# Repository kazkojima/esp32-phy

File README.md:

# ESP32 PHY

## hardware

ESP-WROOM-32 board with Ethernet made with KiCAD

  * esp32-tlk110

  * esp32-wslan8720

  There are choices for esp32-wslan8720 board. See 

https://kazkojima.github.io/esp32-phy2.html

for detail.

## apps

Applications with ESP32 PHY.

  * sbusconv - A serial to ether converter

See README in the application directory for detail.

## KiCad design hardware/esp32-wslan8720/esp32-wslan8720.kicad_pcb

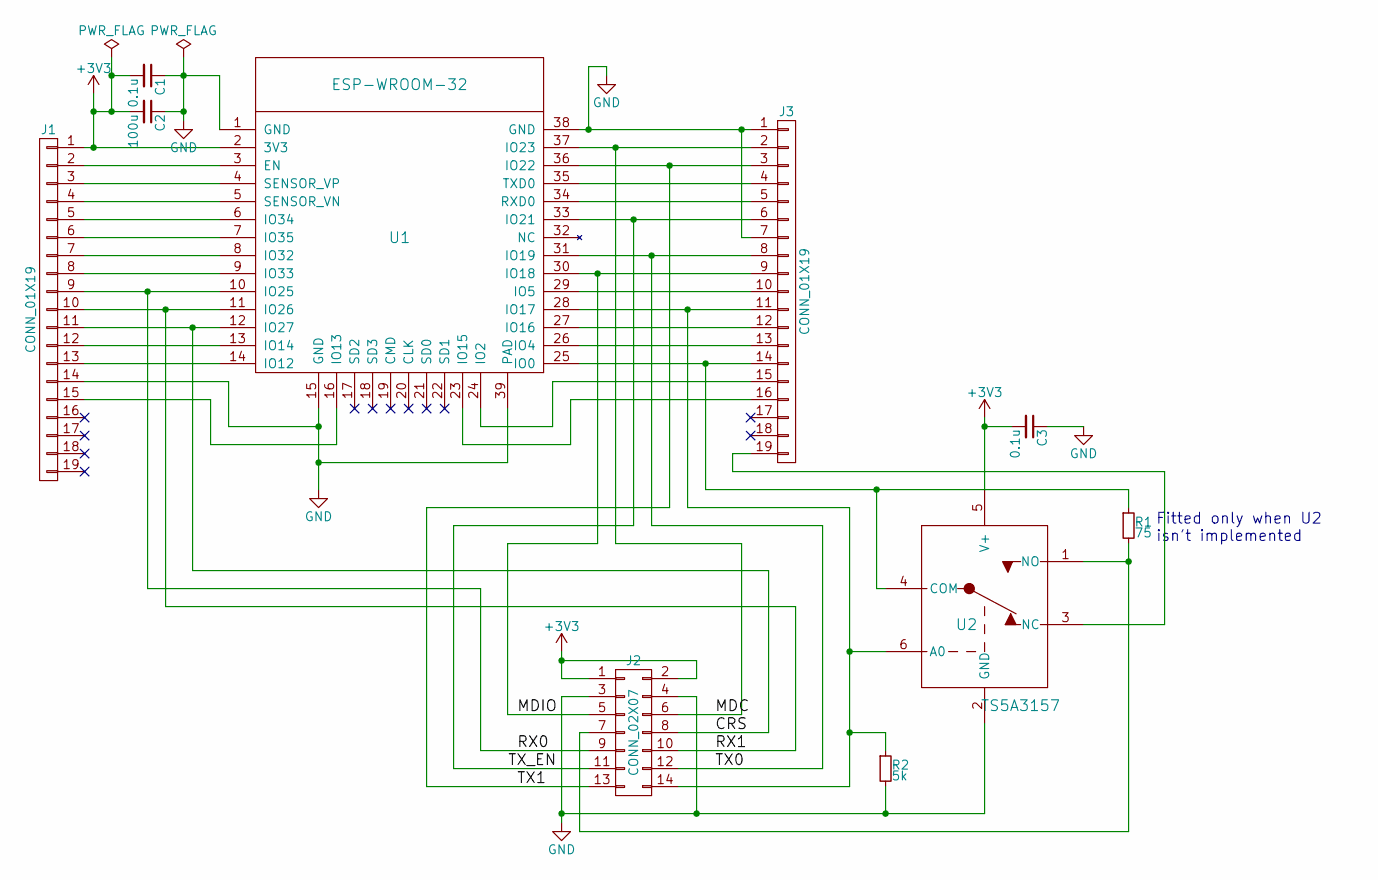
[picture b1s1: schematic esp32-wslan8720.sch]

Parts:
C1, C3: 0.1u; C_0603_HandSoldering
C2: 100u; C_1210_HandSoldering
J1, J3: CONN_01X19; Pin_Header_Straight_1x19_Pitch2.54mm
J2: CONN_02X07; Pin_Header_Angled_2x07_Pitch2.54mm
R1: 75; R_0603_HandSoldering
R2: 5k; R_0603_HandSoldering
U1: ESP-WROOM-32; ESP32-WROOM-fixed
U2: TS5A3157; SOT-23-6_Handsoldering

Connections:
+3V3: C1.2, C2.2, C3.2, J1.1, J2.1, J2.2, U1.2 (3V3), U2.5 (V+)
/CRS: J1.11, J2.8, U1.12 (IO27)
/MDC: J2.6, J3.2, U1.37 (IO23)
/MDIO: J2.5, J3.9, U1.30 (IO18)
/RX0: J1.9, J2.9, U1.10 (IO25)
/RX1: J1.10, J2.10, U1.11 (IO26)
/TX0: J2.12, J3.8, U1.31 (IO19)
/TX1: J2.13, J3.3, U1.36 (IO22)
/TX_EN: J2.11, J3.6, U1.33 (IO21)
GND: C1.1, C2.1, C3.1, J1.14, J2.3, J2.4, J3.1, J3.7, R2.2, U1.1 (GND), U1.15 (GND), U1.38 (GND), U1.39 (PAD), U2.2 (GND)
unnamed: J1.2, U1.3 (EN)
unnamed: J1.3, U1.4 (SENSOR_VP)
unnamed: J1.4, U1.5 (SENSOR_VN)
unnamed: J1.5, U1.6 (IO34)
unnamed: J1.6, U1.7 (IO35)
unnamed: J1.7, U1.8 (IO32)
unnamed: J1.8, U1.9 (IO33)
unnamed: J1.12, U1.13 (IO14)
unnamed: J1.13, U1.14 (IO12)
unnamed: J1.15, U1.16 (IO13)
unnamed: J2.7, R1.2, U2.1 (NO)
unnamed: J2.14, J3.11, R2.1, U1.28 (IO17), U2.6 (A0)
unnamed: J3.4, U1.35 (TXD0)
unnamed: J3.5, U1.34 (RXD0)
unnamed: J3.10, U1.29 (IO5)
unnamed: J3.12, U1.27 (IO16)
unnamed: J3.13, U1.26 (IO4)
unnamed: J3.14, R1.1, U1.25 (IO0), U2.4 (COM)
unnamed: J3.15, U1.24 (IO2)
unnamed: J3.16, U1.23 (IO15)
unnamed: J3.19, U2.3 (NC)

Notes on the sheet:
Fitted only when U2 isn't implemented

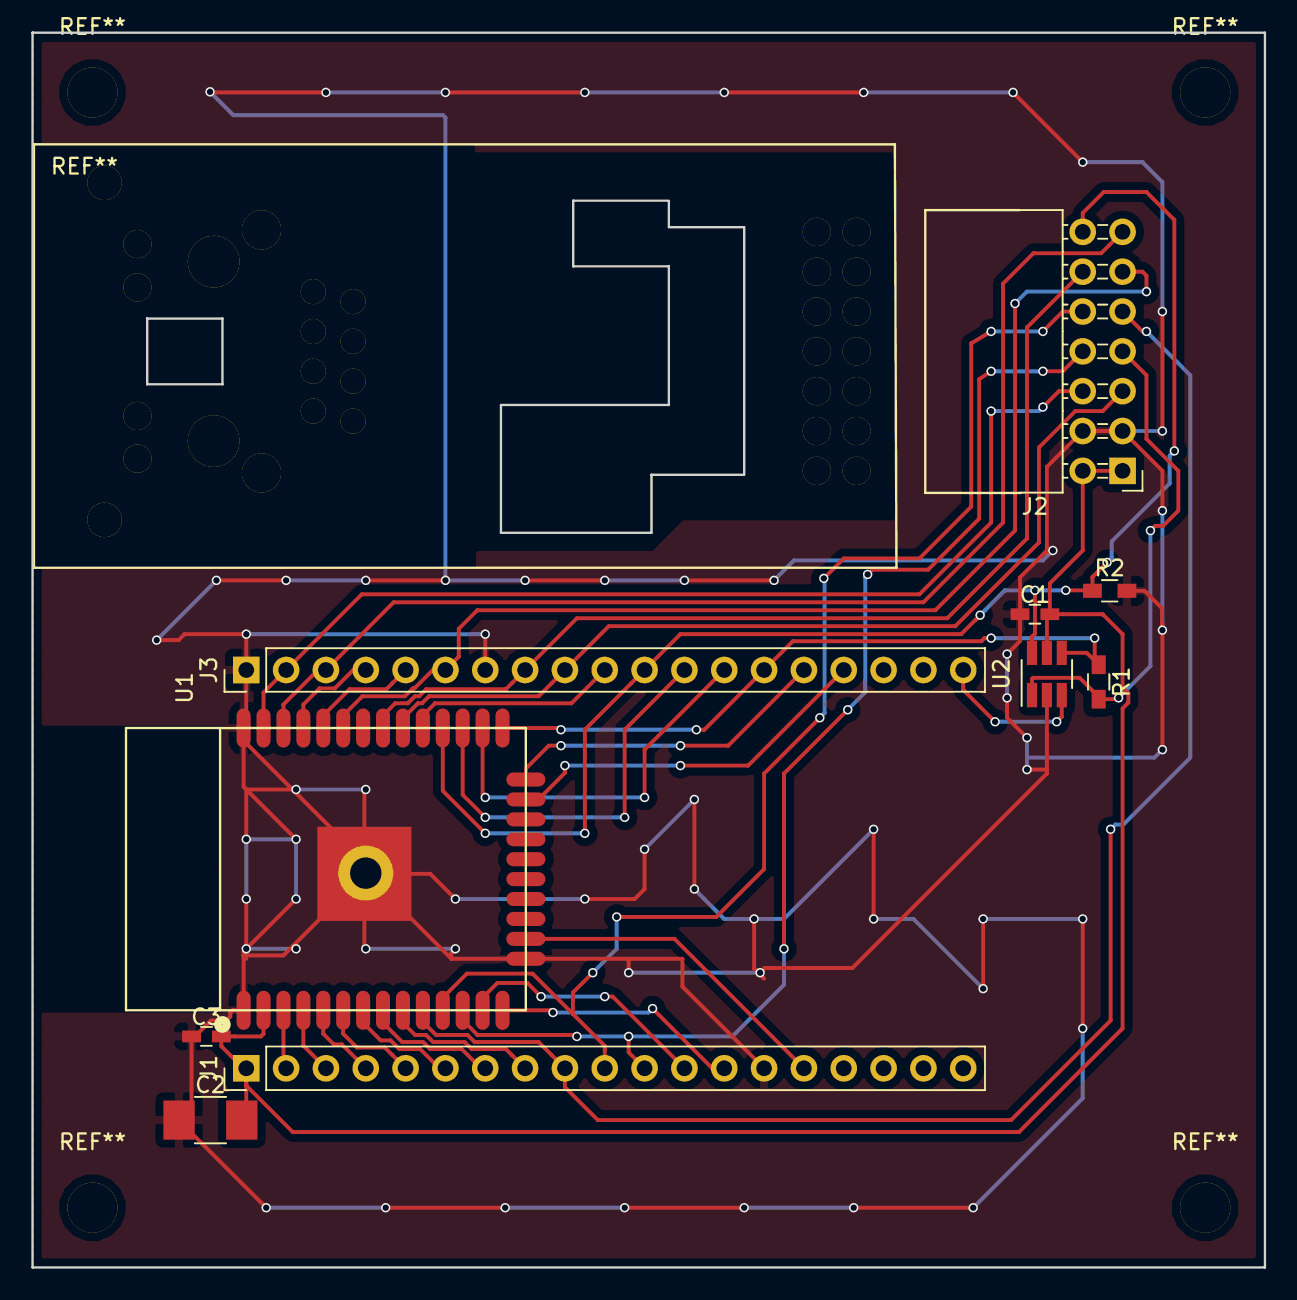
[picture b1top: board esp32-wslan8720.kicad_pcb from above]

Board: 2 copper layers, 78.6 x 78.8 mm, 10 parts (0 on the bottom side), 31 nets.

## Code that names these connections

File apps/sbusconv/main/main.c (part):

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    // RMII data pins are fixed:
    // TXD0 = GPIO19
    // TXD1 = GPIO22
    // TX_EN = GPIO21
    // RXD0 = GPIO25
    // RXD1 = GPIO26
    // CLK == GPIO0
    phy_rmii_configure_data_interface_pins();
    // MDC is GPIO 23, MDIO is GPIO 18
    phy_rmii_smi_configure_pins(PIN_SMI_MDC, PIN_SMI_MDIO);
}

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
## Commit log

2017-10-21 Inital commit
2017-11-07 Add hardware/esp32-wslan8720.
2018-07-24 Add apps directory and sbusconv application.
